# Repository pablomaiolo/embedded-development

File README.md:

This repository contains two projects:

* LoRa32 Sensor Board.
* LIS3MDL driver and application example.

Refer to README.md in each project for a detailed description.

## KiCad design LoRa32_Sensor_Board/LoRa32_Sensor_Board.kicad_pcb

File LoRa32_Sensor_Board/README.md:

LoRa32 Sensor Board
===================
This is a battery powered board that features a MPL115A1 absolute pressure sensor, a LSM303C inertial measurement unit (IMU) and a SAM-M8Q GPS module. This board also has a battery monitor IC, STC3100, which allows to obtain an estimate of the remaining charge. It is meant to be used with TTGO LoRa32 MCU module. The board is powered by a 3.7 V 2200 mAh 18650 battery.

KiCad version 5.0 design files are supplied.

TTGO LoRa32
-----------
LoRa32 is a development board based on the ESP32 chip, which combines a 32-bit microcontroller alongside WiFi and Bluetooth modules. LoRa32 also features a SX1276 LoRa transceiver and an OLED display.

ESP32 has 34 GPIO pins which can be mapped to any peripheral. This particular board uses SPI, I2C and UART to communicate with the sensors. According to LoRa32 schematic, one SPI interface is connected to SX1276 and one I2C is connected to the OLED display. I've decided to use these same interfaces with the sensors. Communication with the GPS module is done through UART. One of the UARTs is connected to a CP2102 USB-to-UART bridge, so in order to be able to simultaneously use this UART and receive data from the GPS, I've decided to use another UART. I chose GPIO21 for UART1 TX signal and GPIO22 for UART1 RX because both of these pins are unused in the LoRa32 board and can be assigned to UART1. GPIO23 is the chip select signal for MPL115A1 and GPIO17 is connected to the shutdown pin.

LSM303C IMU
-----------
LSM303C is an IC featuring a 3D accelerometer and magnetometer. It supports both I2C and SPI. The datasheet explains that in order to use I2C, both chip select lines must be held high (tied to Vdd_IO).

Output pins are connected as follows:

* DRDY_MAG (magnetometer data ready) to GPIO35.
* INT_MAG (magnetometer interrupt signal) to GPIO12.
* INT_XL (accelerometer interrupt signal) to GPIO13.

These three GPIO pins can be set up to trigger an interrupt at positive edge.

MPL115A1 pressure sensor
------------------------
MPL115A1 is an absolute pressure sensor with a SPI interface. It has a shutdown pin that puts the sensor into low power mode. ESP32 GPIO pins default to high impedance before initialization, so both chip select and shutdown pin are pulled up to 3V3 to give them a defined level and avoid triggering a spurious communication sequence.

SAM-M8Q GPS module
------------------
This module features a GPS receiver with an embedded patch antenna. It provides both I2C and UART interfaces, although in this board only UART is used.

STC3100 battery monitor
-----------------------
STC3100 monitors voltage, temperature and current of a single-cell battery. It also has a Coulomb counter which can be used to implement a gas gauge to monitor the available battery capacity. Application is based on the example schematic shown in the datasheet. Sense resistor Rcg is chosen to maximise charge and current resolution. In this application, we have the following maximum current consumption:

* LoRa32: 100 mA
* SAM-M8Q: 67 mA
* LSM303C: 450 uA (worst case when adding magnetometer current plus accelerometer current)
* MPL115A1: 10 uA
* STC3100: 100 uA

For the sake of simplicity we will consider the last three to consume 1 mA each. In this case the maximum total current is 170 mA. Full scale voltage on the internal A/D converter of the STC3100 is +/- 80 mV. Since the board does not have a battery charger, 170 mA is the maximum current that will flow through the sense resistor.

Rcg = 80 mV / 170 mA = 0.47 ohm

But ST's application note [AN3064](https://www.st.com/content/ccc/resource/technical/document/application_note/fa/c2/de/32/e8/c9/4e/28/CD00248578.pdf/files/CD00248578.pdf/jcr:content/translations/en.CD00248578.pdf) also provides an equation relating the charge data in mAh to the sense resistor value:

charge data (mAh) = 6.70 \* charge_code / Rcg (mohm)

charge_code is a 16-bit binary number in two's complement. If we want to be able to measure a full discharge, we should find Rcg for 2200 mAh and a charge code of 2^15-1:

Rcg = 6.70 \* 32767 / 2200 mAh = 0.1 ohm

So, we use a 0.1 ohm resistor for Rcg.

Layout considerations
---------------------
PCB design rules are set according to [PCBWay](https://www.pcbway.com) manufacturing process. Minimum track width and clearance are 6 mils (0.1524 mm). Minimum hole size and width of annular ring are, respectively, 0.3 mm and 0.15 mm, so this yields a minimum via diameter of 0.6 mm.

Components are distributed following common design practices, such as placing decoupling capacitor near supply pins.

STC3100 is as near the battery as possible, but temperature readings probably wouldn't be too accurate since the battery sits on a plastic holder. Following guidelines from STC3100 datasheet, GND pin is routed to the ground side of the sense resistor through a dedicated track, in order to avoid voltage drops that would render the measurement inaccurate. BATT+ and BATT- signals have big copper fills to bring them closer to the pads without voltage drops.

Board size is mainly determined by the battery holder and the LoRa32 module.

Dimensions for the exact module could not be found, so a [very similar board](https://www.thethingsnetwork.org/forum/t/big-esp32-sx127x-topic-part-1/10247) was used as [reference](https://www.thethingsnetwork.org/forum/uploads/default/original/2X/b/b570ebe7e0368088bd9e4b77134d340993c46cf5.jpg) to make the footprint, because it has the same hardware and pin distribution.

Bill of Materials
-----------------

| Reference  | Description                              | Quantity |
|------------|------------------------------------------|----------|
| C1, C3, C4 | 100nF X7R 0805 SMD capacitor             | 3        |
| C2         | 10uF SMD aluminum electrolytic capacitor | 1        |
| C5, C6, C7 | 1uF X7R 0805 SMD capacitor               | 3        |
| C8         | 220nF X7R 0805 SMD capacitor             | 1        |
| J1         | Keystone 1042 battery holder             | 1        |
| R1, R2     | 33k 0805 SMD capacitor                   | 2        |
| R3         | 200k 0.1% 0805 SMD capacitor             | 1        |
| R4         | 1k 0805 SMD capacitor                    | 1        |
| R5         | 0.1 1% 0805 SMD capacitor                | 1        |
| U1         | LSM303CTR                                | 1        |
| U2         | 18 pos female rectangular header         | 2        |
| U3         | MPL115A1                                 | 1        |
| U4         | SAM-M8Q                                  | 1        |
| U5         | STC3100IST                               | 1        |

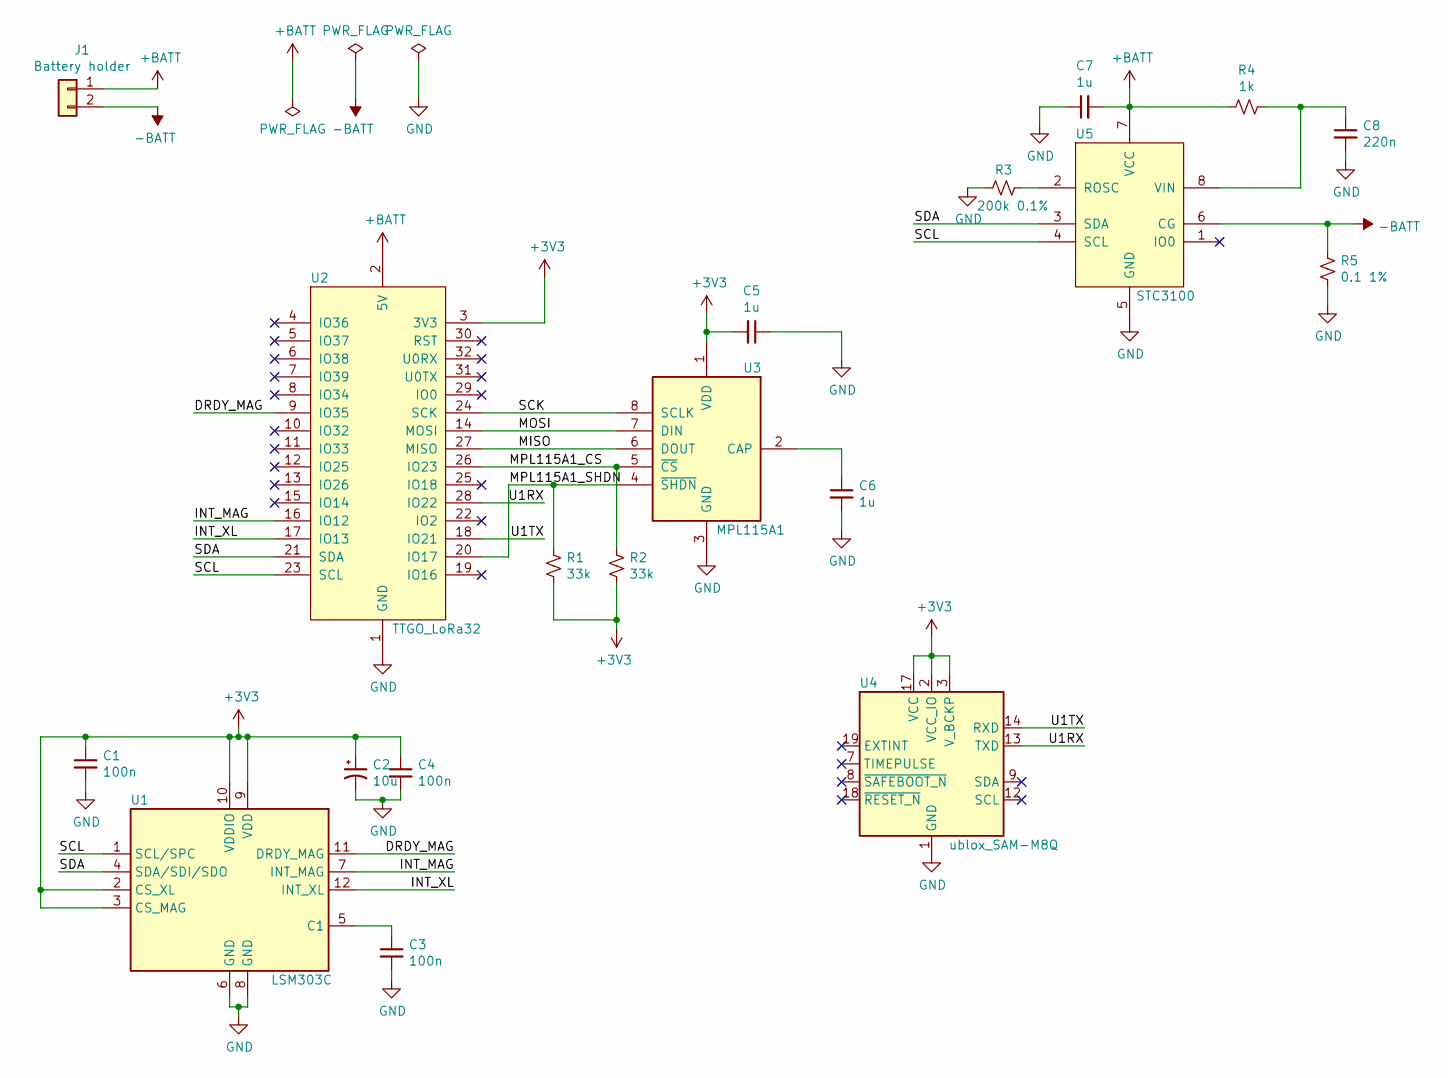
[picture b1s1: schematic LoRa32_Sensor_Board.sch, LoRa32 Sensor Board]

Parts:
C1, C3, C4: 100n; C_0805_2012Metric
C2: 10u; CP_Elec_4x5.4
C5, C6, C7: 1u; C_0805_2012Metric
C8: 220n; C_0805_2012Metric
J1: Battery holder; BatteryHolder_Keystone_1042_1x18650
R1, R2: 33k; R_0805_2012Metric
R3: 200k 0.1%; R_0805_2012Metric
R4: 1k; R_0805_2012Metric
R5: 0.1 1%; R_0805_2012Metric
U1: LSM303C; LGA-12_2x2mm_P0.5mm_smallerpads
U2: TTGO_LoRa32
U3: MPL115A1; LGA-8_3x5mm_P1.25mm
U4: ublox_SAM-M8Q
U5: STC3100; MSOP-8_3x3mm_P0.65mm

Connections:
+3V3: C1.1, C2.1, C4.1, C5.2, R1.2, R2.2, U1.2 (CS_XL), U1.3 (CS_MAG), U1.9 (VDD), U1.10 (VDDIO), U2.3 (3V3), U2.34 (3V3), U3.1 (VDD), U4.2 (VCC_IO), U4.3 (V_BCKP), U4.17 (VCC)
+BATT: C7.2, J1.1, R4.2, U2.2 (5V), U2.35 (5V), U5.7 (VCC)
-BATT: J1.2, R5.1, U5.6 (CG)
/DRDY_MAG: U1.11 (DRDY_MAG), U2.9 (IO35)
/INT_MAG: U1.7 (INT_MAG), U2.16 (IO12)
/INT_XL: U1.12 (INT_XL), U2.17 (IO13)
/MISO: U2.27 (MISO), U3.6 (DOUT)
/MOSI: U2.14 (MOSI), U3.7 (DIN)
/MPL115A1_CS: R2.1, U2.26 (IO23), U3.5 (~CS)
/MPL115A1_SHDN: R1.1, U2.20 (IO17), U3.4 (~SHDN)
/SCK: U2.24 (SCK), U3.8 (SCLK)
/SCL: U1.1 (SCL/SPC), U2.23 (SCL), U5.4 (SCL)
/SDA: U1.4 (SDA/SDI/SDO), U2.21 (SDA), U5.3 (SDA)
/U1RX: U2.28 (IO22), U4.13 (TXD)
/U1TX: U2.18 (IO21), U4.14 (RXD)
GND: C1.2, C2.2, C3.2, C4.2, C5.1, C6.2, C7.1, C8.2, R3.2, R5.2, U1.6 (GND), U1.8 (GND), U2.1 (GND), U2.33 (GND), U2.36 (GND), U3.3 (GND), U4.1 (GND), U4.4 (GND), U4.5 (GND), U4.6 (GND), U4.10 (GND), U4.11 (GND), U4.15 (GND), U4.16 (GND), U4.20 (GND), U5.5 (GND)
unnamed: C3.1, U1.5 (C1)
unnamed: C6.1, U3.2 (CAP)
unnamed: C8.1, R4.1, U5.8 (VIN)
unnamed: R3.1, U5.2 (ROSC)

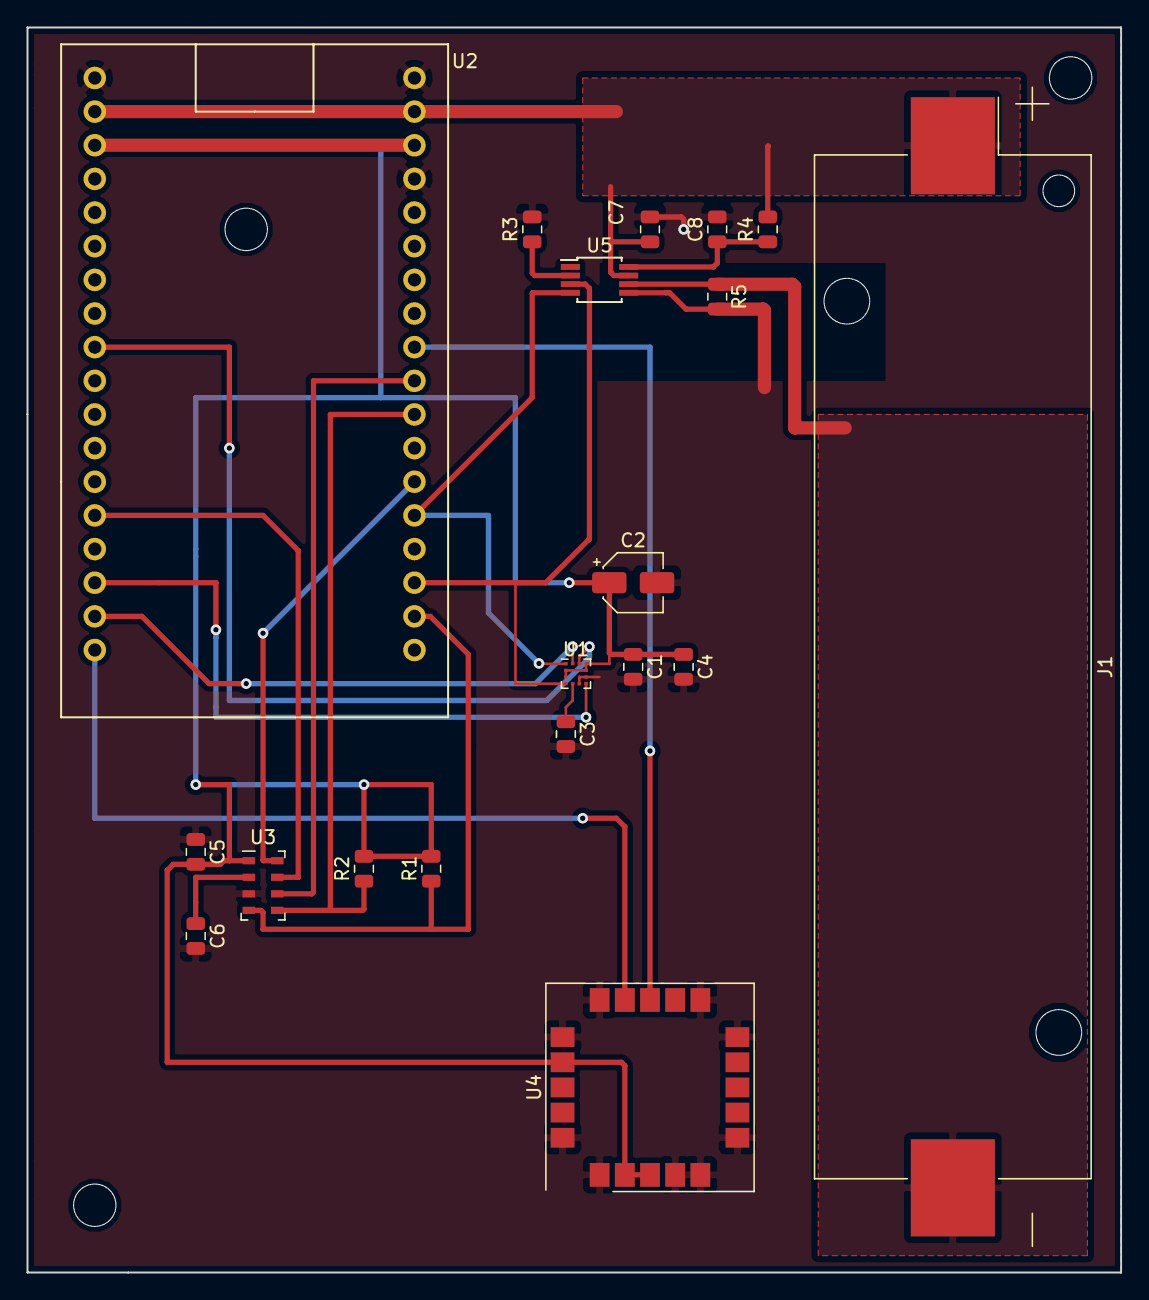
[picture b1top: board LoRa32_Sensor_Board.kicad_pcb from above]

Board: 2 copper layers, 82.6 x 94.0 mm, 19 parts (0 on the bottom side), 20 nets.

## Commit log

2019-04-03 PCB finished
2019-04-04 README.md for the hardware part added, sense resistor tracks widened
2019-04-08 DRDY_MAG, INT_XL and INT_MAG pins from LSM303C connected to ESP32
2019-04-08 Add LIS3MDL sensor project, add mounting holes to board
2019-04-08 Fix in code, useless files deletion, changes in README.md and license added
2019-04-08 Add bill of materials
2019-04-09 Update README.md
    Add LoRa32 footprint info and KiCad version.
